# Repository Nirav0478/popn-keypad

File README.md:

# Pop'n Keypad
This is an unfinished macropad I am working on for the rhythm game [Pop'n Music](https://en.wikipedia.org/wiki/Pop%27n_Music).

## The Problem
To keep it short, because the keys on my laptop tend to ghost their inputs when I press multiple keys at a time, I need to have a dedicated controller to play Pop'n Music. Buying a full controller and making one yourself are both ridiculously expensive, so I instead sought to make a miniature macropad with a very similar layout!

## Goals
Create a working keypad for Pop'n Music
- Bottom row has 5 keys, top row has 4 keys
- Keycaps need to be color coded according to its controller
- I should be able to play on it reasonably well
- Hot swappable keyswitches
- Vertically as short as possible

## Supplies
- Arduino Micro
- Custom PCB
- Colored keycaps
- Hot swap plugs
- Keyswitches (clicky)
- 3d printed case
- 4x screws, nuts, and washers

## My Design process
1. Made some simple paper sketches of what exactly I am looking for.
2. I watched various tutorials on YouTube about using KiCad to make keyboard PCBs.
3. Prototyped a rudimentary outline on TinkerCad.
4. Designed a PCB on Kicad
5. Currently creating a 3D-printed case on Onshape based on the PCB

to be continued...

## [Onshape Link](https://cad.onshape.com/documents/f7e567a801d71e2f8f1533ab/w/61ac0e9fbb2c20d94dde86a0/e/666452ca24dc6e20860be091?renderMode=0&uiState=69a9eb1542bac0e2952504f7)

## Gallery
Coming soon!

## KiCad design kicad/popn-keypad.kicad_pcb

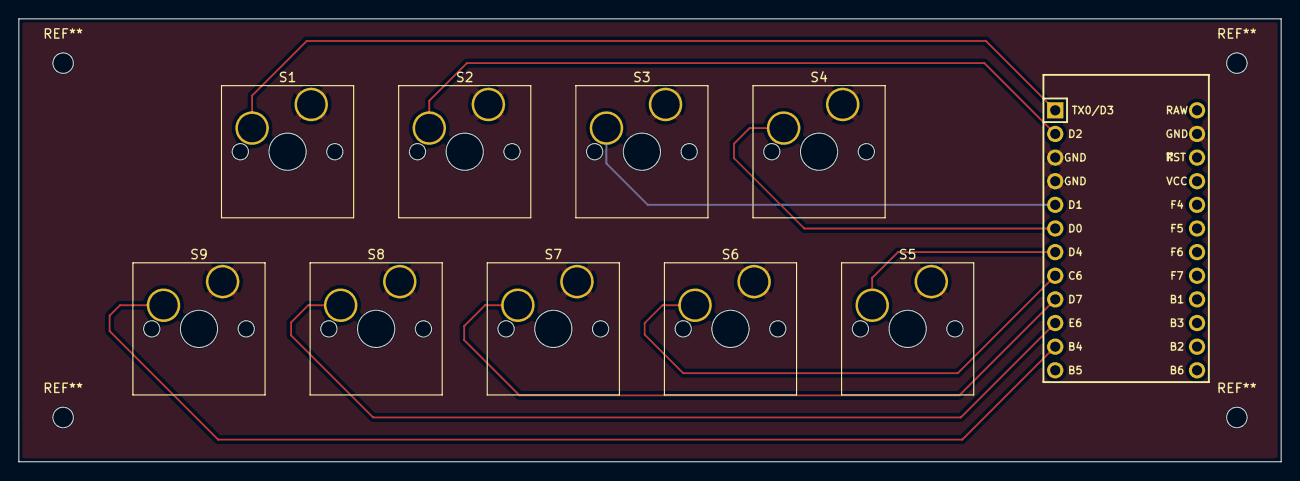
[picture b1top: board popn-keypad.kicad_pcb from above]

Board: 2 copper layers, 135.7 x 47.6 mm, 10 parts (0 on the bottom side), 10 nets.

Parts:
S1, S2, S3, S4, S5, S6, S7, S8, S9: Hotswap_MX_Plated_1.00u
U1: Arduino_Pro_Micro

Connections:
GND: S1.2, S2.2, S3.2, S4.2, S5.2, S6.2, S7.2, S8.2, S9.2, U1.3 (GND), U1.4 (GND), U1.23 (GND)
S1: S1.1, U1.1 (TX0/PD3)
S2: S2.1, U1.2 (RX1/PD2)
S3: S3.1, U1.5 (2/PD1)
S4: S4.1, U1.6 (3/PD0)
S5: S5.1, U1.7 (4/PD4)
S6: S6.1, U1.8 (5/PC6)
S7: S7.1, U1.9 (6/PD7)
S8: S8.1, U1.10 (7/PE6)
S9: S9.1, U1.11 (8/PB4)

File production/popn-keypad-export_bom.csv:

Designator,Footprint,Quantity,Value,LCSC Part #
"S1, S2, S3, S4, S5, S6, S7, S8, S9",Hotswap_MX_Plated_1.00u,9,~,
U1,Arduino_Pro_Micro,1,Arduino_Pro_Micro,

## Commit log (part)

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2026-01-12 Add Wikipedia link to Pop'n Music in README
2026-01-24 Defined edge cuts, added filled zones
2026-01-24 Hotfix
2026-02-11 Generated export files
2026-02-14 Re-exported some files
2026-02-14 Major rewiring
    I got rid of all of my ground lines in favor of a copper fill connected to ground. This made the routing my traces far less convoluted.
2026-02-15 Fixed error
    Fixed "Thermal relief connection to zone incomplete" error on the ground pin on S9.
2026-02-15 Updated production files
    Updated the production files with the changes from the previous commit
2026-02-15 Added mounting holes, adjusted dimensions
    Added M2 mounting holes to the board, reduced the height of it (adjusting the traces as needed). Rebuilt production files.
2026-02-15 quick fix
    Fixed warnings that came up as a result of the previous commit
2026-02-15 Adjusted keypad dimensions
    Made the keypad wider, to better accommodate for the mount holes and the case
2026-02-25 Exported .step file
2026-02-25 Reorganized files
    Reorganized the directory structure of the repo to make room for potential Onshape export files. All Kicad-related files are now in the "kicad" folder.
2026-03-05 Redesigned board
    Moved the microcontroller farther away from the keys. Also re-routed my traces to be further from any holes on the board.
2026-03-05 Add Onshape link to README
    Added a link to the Onshape document for the 3D-printed case.
2026-03-07 Re-exported production files
2026-03-09 Exported STEP file, new .md file
    Re-exported STEP file for bottom plate, and added a new .md file for my shopping list to bring the project to reality!
2026-04-11 Changed shopping list, made tweaks to files
2026-04-19 Updated to Kicad 10, renamed some parts for organization
2026-04-19 Add .history folder in kicad to .gitignore
2026-05-20 Brief rebuild
